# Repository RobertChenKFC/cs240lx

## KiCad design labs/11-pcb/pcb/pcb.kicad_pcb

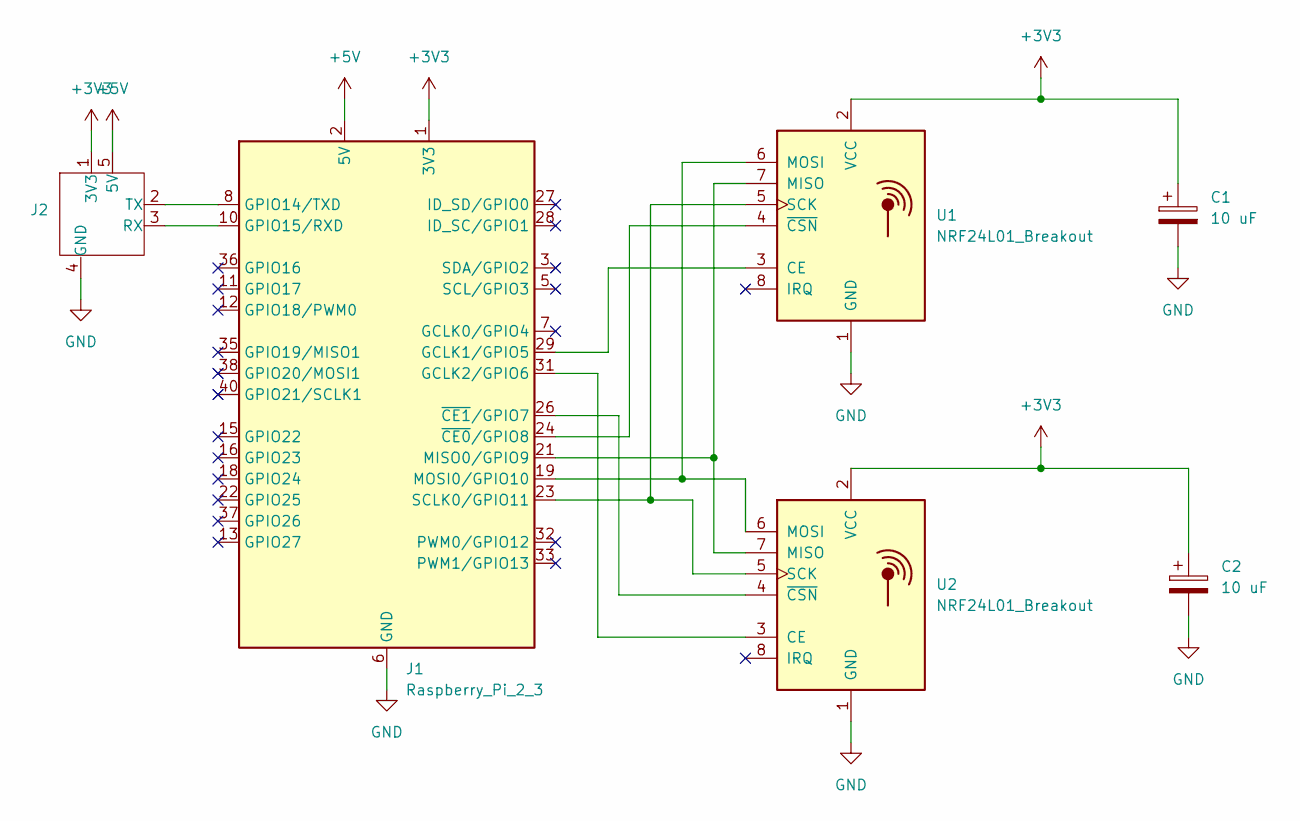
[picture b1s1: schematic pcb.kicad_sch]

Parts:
C1, C2: 10 uF; CP_Elec_4x5.4
J1: Raspberry_Pi_2_3; PinSocket_2x20_P2.54mm_Vertical
J2: PinSocket_1x05_P2.54mm_Horizontal
U1, U2: NRF24L01_Breakout; nRF24L01_Breakout

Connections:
+3V3: C1.1, C2.1, J1.1 (3V3), J1.17 (3V3), J2.1 (3V3), U1.2 (VCC), U2.2 (VCC)
+5V: J1.2 (5V), J1.4 (5V), J2.5 (5V)
GND: C1.2, C2.2, J1.6 (GND), J1.9 (GND), J1.14 (GND), J1.20 (GND), J1.25 (GND), J1.30 (GND), J1.34 (GND), J1.39 (GND), J2.4 (GND), U1.1 (GND), U2.1 (GND)
unnamed: J1.29 (GCLK1/GPIO5), U1.3 (CE)
unnamed: J1.31 (GCLK2/GPIO6), U2.3 (CE)
unnamed: J1.8 (GPIO14/TXD), J2.2 (TX)
unnamed: J1.10 (GPIO15/RXD), J2.3 (RX)
unnamed: J1.21 (MISO0/GPIO9), U1.7 (MISO), U2.7 (MISO)
unnamed: J1.19 (MOSI0/GPIO10), U1.6 (MOSI), U2.6 (MOSI)
unnamed: J1.23 (SCLK0/GPIO11), U1.5 (SCK), U2.5 (SCK)
unnamed: J1.24 (~CE0/GPIO8), U1.4 (~CSN)
unnamed: J1.26 (~CE1/GPIO7), U2.4 (~CSN)

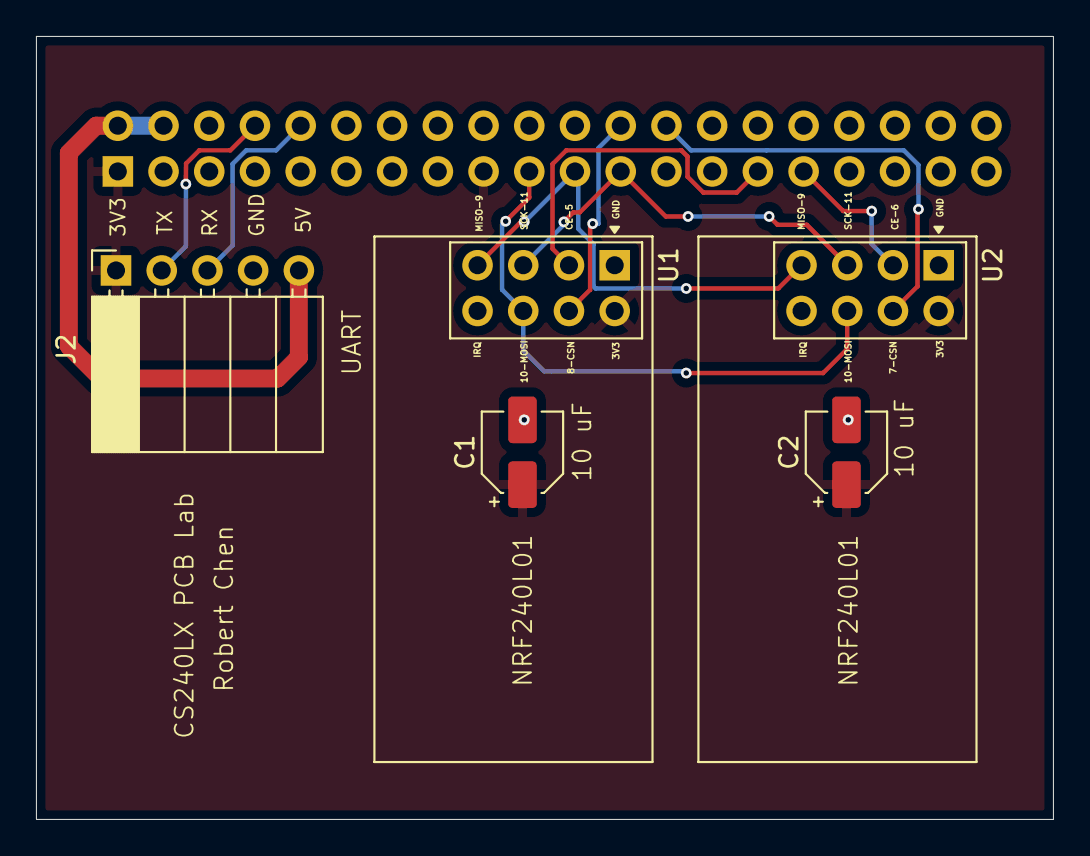
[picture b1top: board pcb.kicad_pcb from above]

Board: 2 copper layers, 56.5 x 43.5 mm, 6 parts (1 on the bottom side), 12 nets.

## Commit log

2024-04-19 implemented lab 1
2024-04-19 implemented lab 2
2024-04-19 implemented lab 3
2024-04-19 implemented lab 4
2024-04-24 implemented lab 6
2024-04-26 implemented lab 5
2024-05-02 modified ir to work with new remote
2024-05-21 implemented lab 7
2024-05-21 implemented lab 8
2024-05-21 implemented lidar
2024-05-21 added new makefiles for testing purposes
2024-05-21 implemented lab 11
2024-05-21 added gpio networking
2024-05-21 implemented working JTAG probe
2024-05-21 modified jtag code to be more modular
2024-05-22 added gdb server
2024-05-24 implemented lab 12
2024-05-27 implemented register, memory, and single stepping for debugger
2024-05-27 pcb stuff
2024-05-27 implemented breakpoints for debugger
2024-05-29 implemented lab 10
2024-05-30 added lock-free data structures implemented by chatgpt
2024-09-10 added README.md for JTAG debugger
2025-09-23 Update debugger for better instruction
